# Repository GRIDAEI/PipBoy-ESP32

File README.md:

# Pip-Boy 3000 - ESP32-S3 Replica OS ☢️

Projekt ma na celu jak najdokładniejsze odtworzenie kultowego urządzenia z serii gier Fallout.
**Pip-Boy 3000**, znany głównie z _Fallout 3_ oraz _Fallout: New Vegas_, zyskuje tu nowe życie dzięki mikrokontrolerowi ESP32-S3. Projekt łączy oprogramowanie (UI/UX) z fizycznym sprzętem, tworząc realistyczny rekwizyt.

## Funkcje

- **Płynny Interfejs i Animacje**: Wykorzystanie biblioteki [LovyanGFX](https://github.com/lovyan03/LovyanGFX) zapewnia wysoką wydajność renderowania na ekranie.
- **System Audio I2S**: Autentyczne efekty dźwiękowe interfejsu (kliknięcia, przejścia w menu) odtwarzane przez `ESP8266Audio` i miksowane w czasie rzeczywistym.
- **Pełna Nawigacja**: Enkoder obrotowy, przełącznik obrotowy oraz fizyczne przyciski idealnie zmapowane, co pozwala na nawigację po zakładkach Statystyk, Ekwipunku i Danych, dokładnie tak jak w grze.
- **Ładowanie Obrazów do PSRAM**: Wysokiej rozdzielczości sprite'y (mapy, przedmioty) ładowane dynamicznie do 8MB pamięci PSRAM w celu oszczędzania pamięci RAM.
- **Zegar Czasu Rzeczywistego (RTC)**: Zegar systemowy z możliwością dostosowania i zapisem w pamięci NVS, odporny na restarty.
- **Motywy Kolorystyczne**: Obsługa różnych kolorów interfejsu (Klasyczny Zielony, Bursztynowy, Quantum Blue).
- **Oszczędzanie Energii**: Inteligentne wykrywanie bezczynności obniża taktowanie procesora do 80MHz, by oszczędzać baterię podczas długich wędrówek po Pustkowiach.

## Gotowe Płytki PCB

W projekcie zawarto pliki produkcyjne dla autorskich płytek drukowanych (PCB). Dostępne są **2 wersje** płytki, z czego **najnowsza rewizja v3.0 jest wysoce zalecana** ze względu na znaczne poprawki stabilności układu.

## Dokumentacja Projektu

Szczegółowe informacje techniczne oraz instrukcje zostały wydzielone do osobnych plików, aby ułatwić nawigację po repozytorium:

- **[Sprzęt i Elektronika (Hardware)](docs/HARDWARE.md)** – schemat układu, kompletna lista komponentów (BOM), tabela podłączeń pinów oraz informacje o zastosowanych modułach (wibracje, DAC).
- **[Architektura Oprogramowania (Software)](docs/SOFTWARE.md)** – objaśnienie działania interfejsu wizualnego (LovyanGFX), buforowanie tekstur w PSRAM, obsługa przerwań enkodera oraz zarządzanie dźwiękiem z LittleFS.
- **[Instrukcja Budowy (Build Guide)](docs/BUILD_GUIDE.md)** – przewodnik krok po kroku, jak skompilować projekt, skonfigurować środowisko PlatformIO i wgrać wymagany obraz pamięci Flash.

## 📁 Struktura Projektu

- `/src/screens/` - Logika odpowiedzialna za poszczególne zakładki interfejsu (Status, S.P.E.C.I.A.L, Ekwipunek, Mapy).
- `/src/modules/` - Sterowniki modułów takich jak Audio (I2S), Enkoder i obsługa karty SD.
- `/src/imgs/` - Tekstury, sprite'y i tablice z grafikami przygotowanymi do użycia.
- `/docs/` - Rozszerzona dokumentacja techniczna projektu.
- `main.cpp` - Główna pętla programu, sekwencja startowa (Boot OS) i dystrybucja wejść.

## Licencja

To jest projekt fanowski. _Pip-Boy_, _Vault Boy_ oraz _Fallout_ są zarejestrowanymi znakami towarowymi Bethesda Softworks LLC. Projekt został stworzony wyłącznie w celach edukacyjnych oraz hobbystycznych (cosplay).

---

_"Prepared for the Future"_ -- Vault-Tec Corporation

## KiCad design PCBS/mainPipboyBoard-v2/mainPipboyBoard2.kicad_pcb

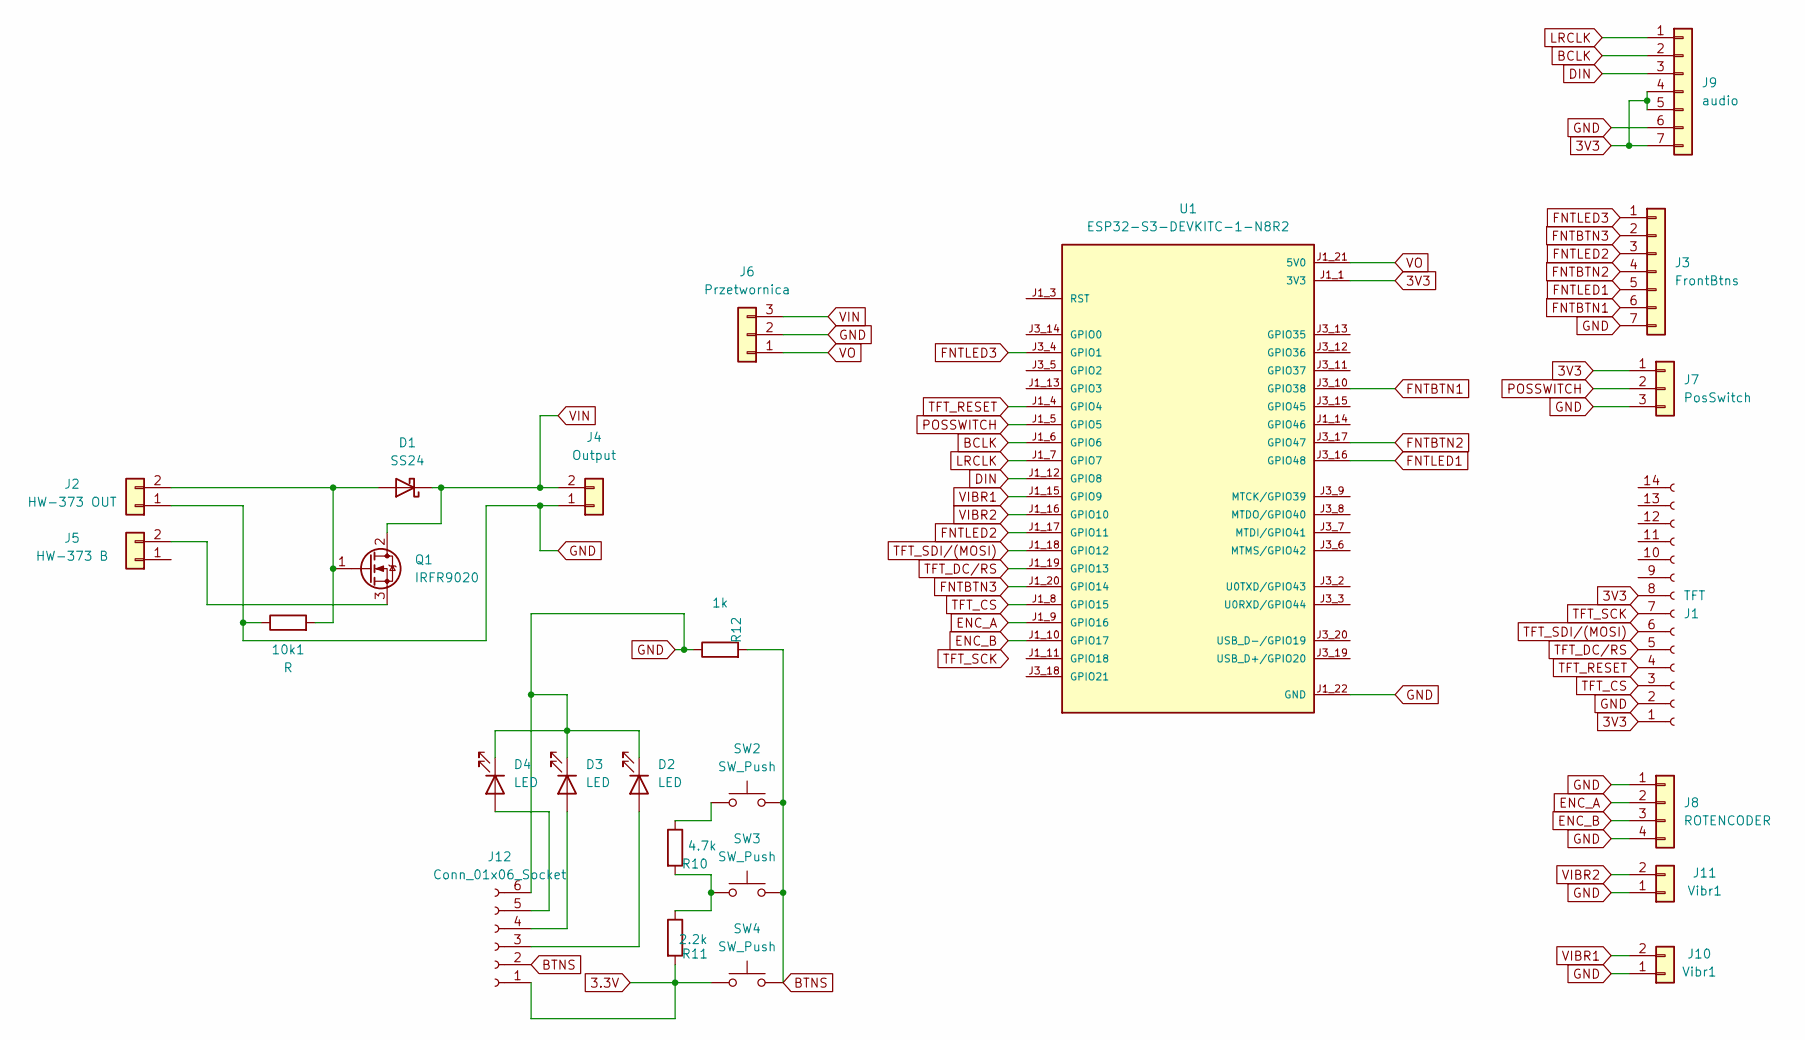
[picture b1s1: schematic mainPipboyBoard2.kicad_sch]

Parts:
10k1: R; R_1206_3216Metric_Pad1.30x1.75mm_HandSolder
D1: SS24; D_SMA
D2, D3, D4: LED; LED_1206_3216Metric_Pad1.42x1.75mm_HandSolder
J1: TFT; PinSocket_1x14_P2.54mm_Vertical
J2: HW-373 OUT; PinSocket_1x02_P2.54mm_Vertical
J3: FrontBtns; PinSocket_1x07_P2.54mm_Vertical
J4: Output; PinSocket_1x02_P2.54mm_Vertical
J5: HW-373 B; PinSocket_1x02_P2.54mm_Vertical
J6: Przetwornica; PinSocket_1x03_P2.54mm_Vertical
J7: PosSwitch; PinSocket_1x03_P2.54mm_Vertical
J8: ROTENCODER; PinSocket_1x04_P2.54mm_Vertical
J9: audio; PinSocket_1x07_P2.54mm_Vertical
J10, J11: Vibr1; PinSocket_1x02_P2.54mm_Vertical
J12: Conn_01x06_Socket; PinHeader_1x06_P2.54mm_Vertical_SMD_Pin1Right
Q1: IRFR9020; TO-252-2
R10: 4.7k; L_1206_3216Metric_Pad1.22x1.90mm_HandSolder
R11: 2.2k; L_1206_3216Metric_Pad1.22x1.90mm_HandSolder
R12: 1k; L_1206_3216Metric_Pad1.22x1.90mm_HandSolder
SW2, SW3, SW4: SW_Push; PTS810SJM250SMTRLFS
U1: ESP32-S3-DEVKITC-1-N8R2; XCVR_ESP32-S3-DEVKITC-1-N8R2; PARTREV V1

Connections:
3.3V: J12.1, R11.2, SW4.1
3V3: J1.1, J1.8, J7.1, J9.4, J9.5, J9.7, U1.J1_1 (3V3), U1.J1_2 (3V3)
BCLK: J9.2, U1.J1_6 (GPIO6)
BTNS: J12.2, R12.2, SW2.2, SW3.2, SW4.2
DIN: J9.3, U1.J1_12 (GPIO8)
ENC_A: J8.2, U1.J1_9 (GPIO16)
ENC_B: J8.3, U1.J1_10 (GPIO17)
FNTBTN1: J3.6, U1.J3_10 (GPIO38)
FNTBTN2: J3.4, U1.J3_17 (GPIO47)
FNTBTN3: J3.2, U1.J1_20 (GPIO14)
FNTLED1: J3.5, U1.J3_16 (GPIO48)
FNTLED2: J3.3, U1.J1_17 (GPIO11)
FNTLED3: J3.1, U1.J3_4 (GPIO1)
GND: 10k1.1, D2.1 (K), D3.1 (K), D4.1 (K), J1.2, J2.1, J3.7, J4.1, J6.2, J7.3, J8.1, J8.4, J9.6, J10.1, J11.1, J12.6, R12.1, U1.J1_22 (GND), U1.J3_1 (GND), U1.J3_21 (GND), U1.J3_22 (GND)
LRCLK: J9.1, U1.J1_7 (GPIO7)
unnamed: 10k1.2, D1.2 (A), J2.2, Q1.1 (G)
unnamed: D2.2 (A), J12.3
unnamed: D3.2 (A), J12.4
unnamed: D4.2 (A), J12.5
unnamed: J5.2 (Pin_2_2), Q1.3 (S)
unnamed: R10.1, SW2.1
unnamed: R10.2, R11.1, SW3.1
POSSWITCH: J7.2, U1.J1_5 (GPIO5)
TFT_CS: J1.3, U1.J1_8 (GPIO15)
TFT_DC/RS: J1.5, U1.J1_19 (GPIO13)
TFT_RESET: J1.4, U1.J1_4 (GPIO4)
TFT_SCK: J1.7
TFT_SDI/(MOSI): J1.6, U1.J1_18 (GPIO12)
VIBR1: J10.2, U1.J1_15 (GPIO9)
VIBR2: J11.2, U1.J1_16 (GPIO10)
VIN: D1.1 (K), J4.2, J6.3, Q1.2 (D)
VO: J6.1, U1.J1_21 (5V0)

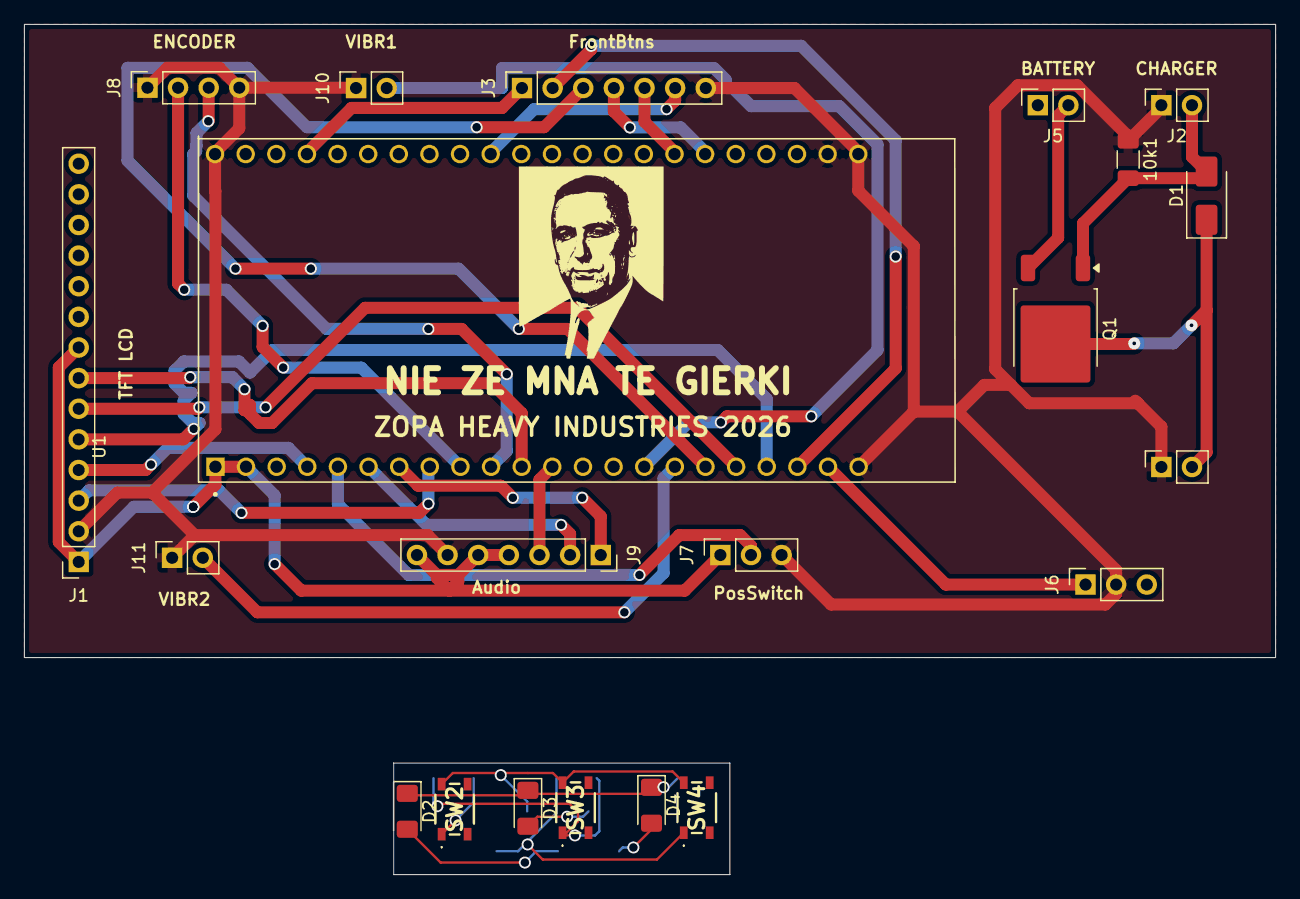
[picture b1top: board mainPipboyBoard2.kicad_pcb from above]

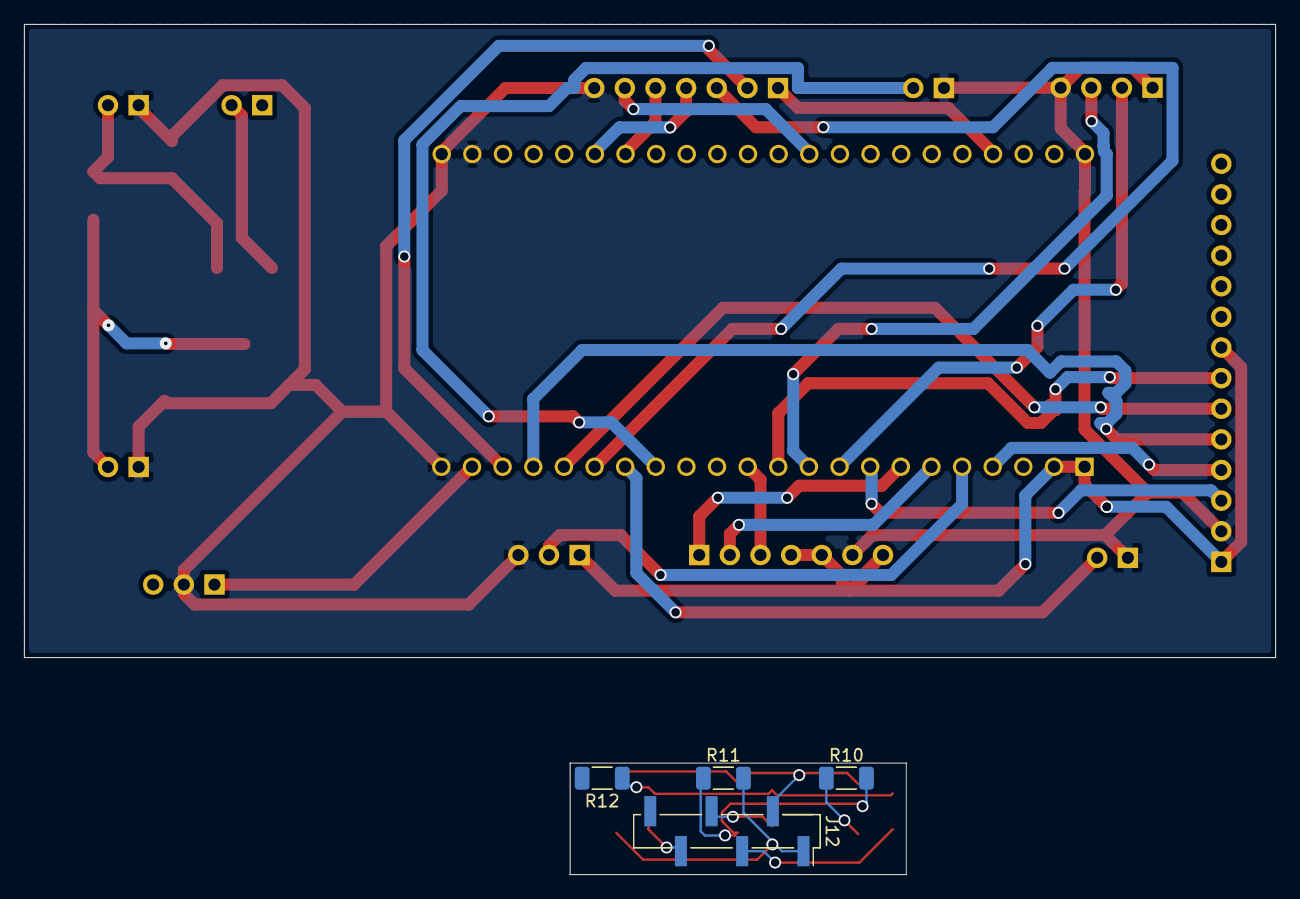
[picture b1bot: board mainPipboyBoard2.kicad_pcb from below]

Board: 2 copper layers, 103.8 x 70.5 mm, 25 parts (4 on the bottom side), 31 nets.

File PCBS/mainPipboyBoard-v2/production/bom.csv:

Designator,Footprint,Quantity,Value,LCSC Part #
10K1,1206,1,R,
D1,D_SMA,1,SS24,
J1,PinSocket_1x14_P2.54mm_Vertical,1,TFT,
"J10, J11",PinSocket_1x02_P2.54mm_Vertical,2,Vibr1,
J2,PinSocket_1x02_P2.54mm_Vertical,1,HW-373 OUT,
J3,PinSocket_1x07_P2.54mm_Vertical,1,FrontBtns,
J4,PinSocket_1x02_P2.54mm_Vertical,1,Output,
J5,PinSocket_1x02_P2.54mm_Vertical,1,HW-373 B,
J6,PinSocket_1x03_P2.54mm_Vertical,1,Przetwornica,
J7,PinSocket_1x03_P2.54mm_Vertical,1,PosSwitch,
J8,PinSocket_1x04_P2.54mm_Vertical,1,Conn_01x04,
J9,PinSocket_1x07_P2.54mm_Vertical,1,audio,
Q1,TO-252-2,1,IRFR9020,
U1,XCVR_ESP32-S3-DEVKITC-1-N8R2,1,ESP32-S3-DEVKITC-1-N8R2,

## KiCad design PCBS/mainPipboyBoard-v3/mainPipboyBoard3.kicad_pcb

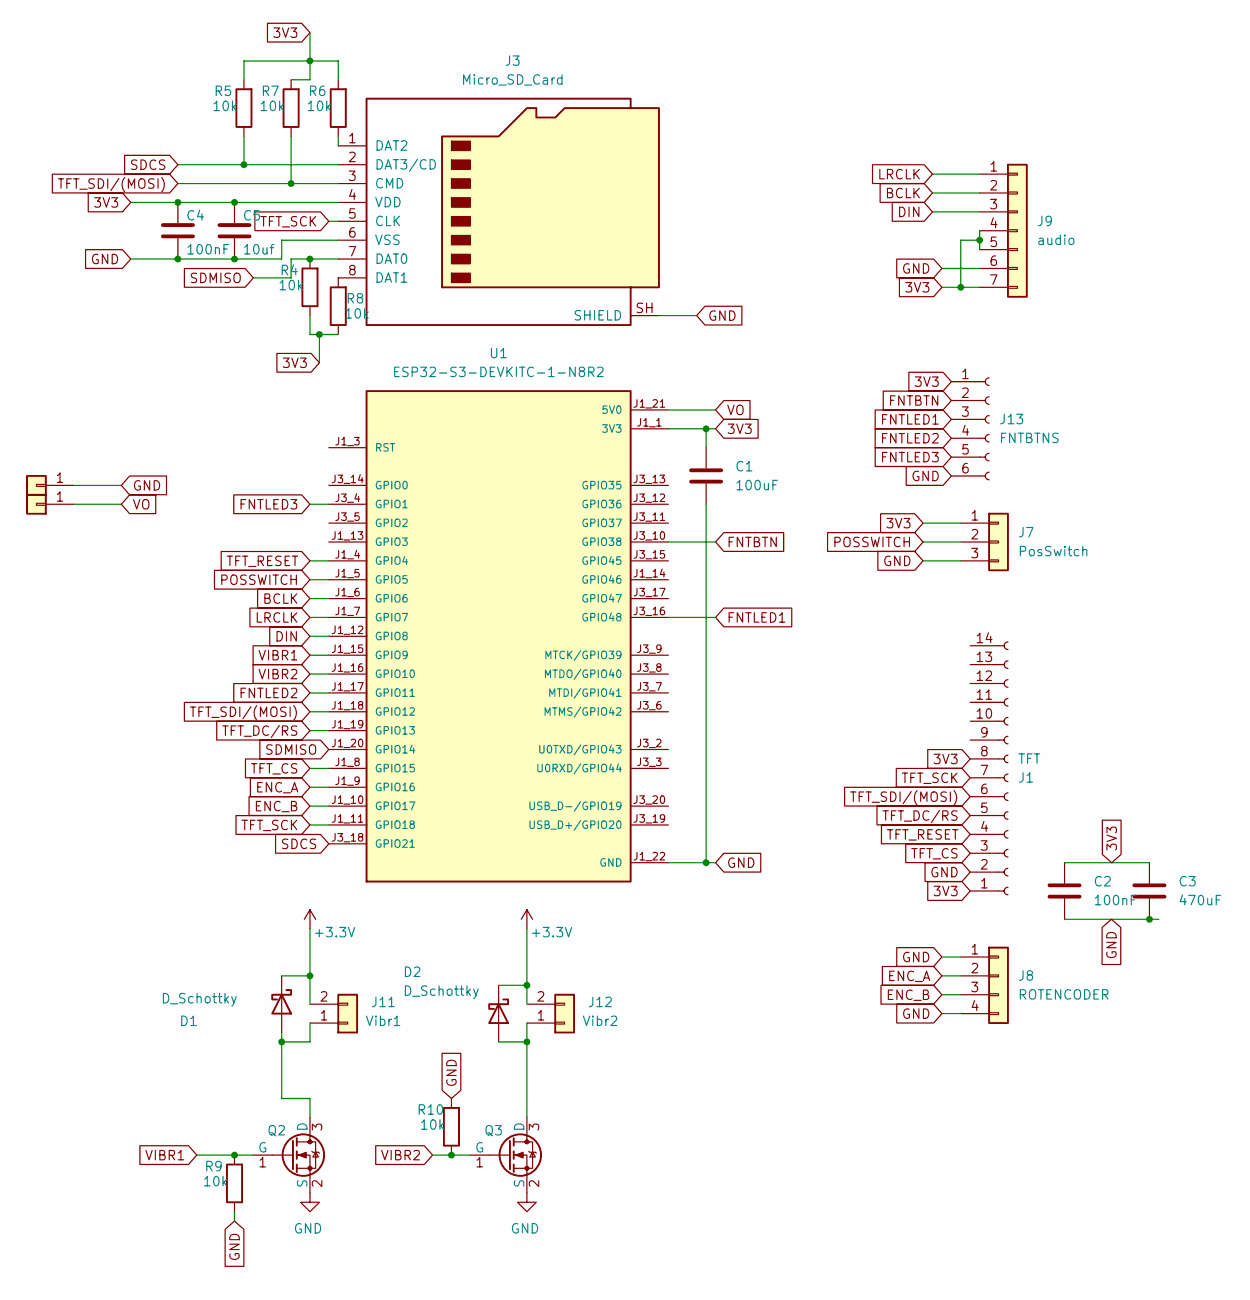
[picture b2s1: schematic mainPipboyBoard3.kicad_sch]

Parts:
C1: 100uF; C_Radial_D4.0mm_H5.0mm_P1.50mm
C2: 100nF; C_0805_2012Metric_Pad1.18x1.45mm_HandSolder
C3: 470uF; C_Radial_D4.0mm_H5.0mm_P1.50mm
C4: 100nF; L_1206_3216Metric_Pad1.22x1.90mm_HandSolder
C5: 10uf; L_1206_3216Metric_Pad1.22x1.90mm_HandSolder
D1, D2: D_Schottky; D_1206_3216Metric_Pad1.42x1.75mm_HandSolder
J1: TFT; PinSocket_1x14_P2.54mm_Vertical
J2, J4: Conn_01x01; PinSocket_1x01_P2.54mm_Vertical
J3: Micro_SD_Card; 112JTDARR01
J7: PosSwitch; PinSocket_1x03_P2.54mm_Vertical
J8: ROTENCODER; PinSocket_1x04_P2.54mm_Vertical
J9: audio; PinSocket_1x07_P2.54mm_Vertical
J11: Vibr1; PinSocket_1x02_P2.54mm_Vertical
J12: Vibr2; PinSocket_1x02_P2.54mm_Vertical
J13: FNTBTNS; JST_ZH_B6B-ZR-SM4-TF_1x06-1MP_P1.50mm_Vertical
Q2, Q3: AO3400A; SOT-23; Part AO3400A; LCSC Part Number C20917
R4, R5, R6, R7, R8, R9, R10: 10k; L_1206_3216Metric_Pad1.22x1.90mm_HandSolder
U1: ESP32-S3-DEVKITC-1-N8R2; XCVR_ESP32-S3-DEVKITC-1-N8R2; PARTREV V1

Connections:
3V3: C1.2, C2.2, C3.2, C4.1, C5.1, J1.1, J1.8, J3.4 (VDD), J7.1, J9.4, J9.5, J9.7, J13.1, R4.1, R5.2, R6.2, R7.2, R8.1, U1.J1_1 (3V3), U1.J1_2 (3V3)
+3.3V: D1.1 (K), D2.1 (K), J11.2, J12.2
BCLK: J9.2, U1.J1_6 (GPIO6)
DIN: J9.3, U1.J1_12 (GPIO8)
ENC_A: J8.2, U1.J1_9 (GPIO16)
ENC_B: J8.3, U1.J1_10 (GPIO17)
FNTBTN: J13.2, U1.J3_10 (GPIO38)
FNTLED1: J13.3, U1.J3_16 (GPIO48)
FNTLED2: J13.4, U1.J1_17 (GPIO11)
FNTLED3: J13.5, U1.J3_4 (GPIO1)
GND: C1.1, C2.1, C3.1, C4.2, C5.2, J1.2, J3.6 (VSS), J3.SH (SHIELD), J4.1 (Pin_1_1), J7.3, J8.1, J8.4, J9.6, J13.6, Q2.2 (S), Q3.2 (S), R9.1, R10.2, U1.J1_22 (GND), U1.J3_1 (GND), U1.J3_21 (GND), U1.J3_22 (GND)
LRCLK: J9.1, U1.J1_7 (GPIO7)
unnamed: D1.2 (A), J11.1, Q2.3 (D)
unnamed: D2.2 (A), J12.1, Q3.3 (D)
unnamed: J3.8 (DAT1), R8.2
unnamed: J3.1 (DAT2), R6.1
POSSWITCH: J7.2, U1.J1_5 (GPIO5)
SDCS: J3.2 (DAT3/CD), R5.1, U1.J3_18 (GPIO21)
SDMISO: J3.7 (DAT0), R4.2, U1.J1_20 (GPIO14)
TFT_CS: J1.3, U1.J1_8 (GPIO15)
TFT_DC/RS: J1.5, U1.J1_19 (GPIO13)
TFT_RESET: J1.4, U1.J1_4 (GPIO4)
TFT_SCK: J1.7, J3.5 (CLK), U1.J1_11 (GPIO18)
TFT_SDI/(MOSI): J1.6, J3.3 (CMD), R7.1, U1.J1_18 (GPIO12)
VIBR1: Q2.1 (G), R9.2, U1.J1_15 (GPIO9)
VIBR2: Q3.1 (G), R10.1, U1.J1_16 (GPIO10)
VO: J2.1 (Pin_1_1), U1.J1_21 (5V0)

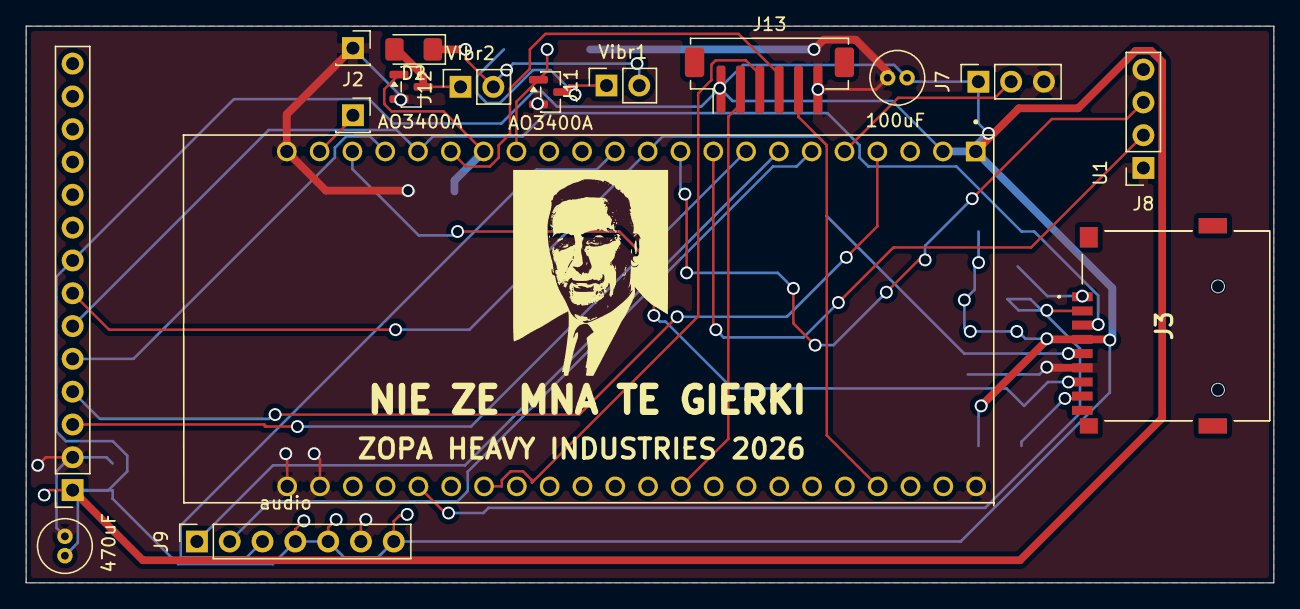
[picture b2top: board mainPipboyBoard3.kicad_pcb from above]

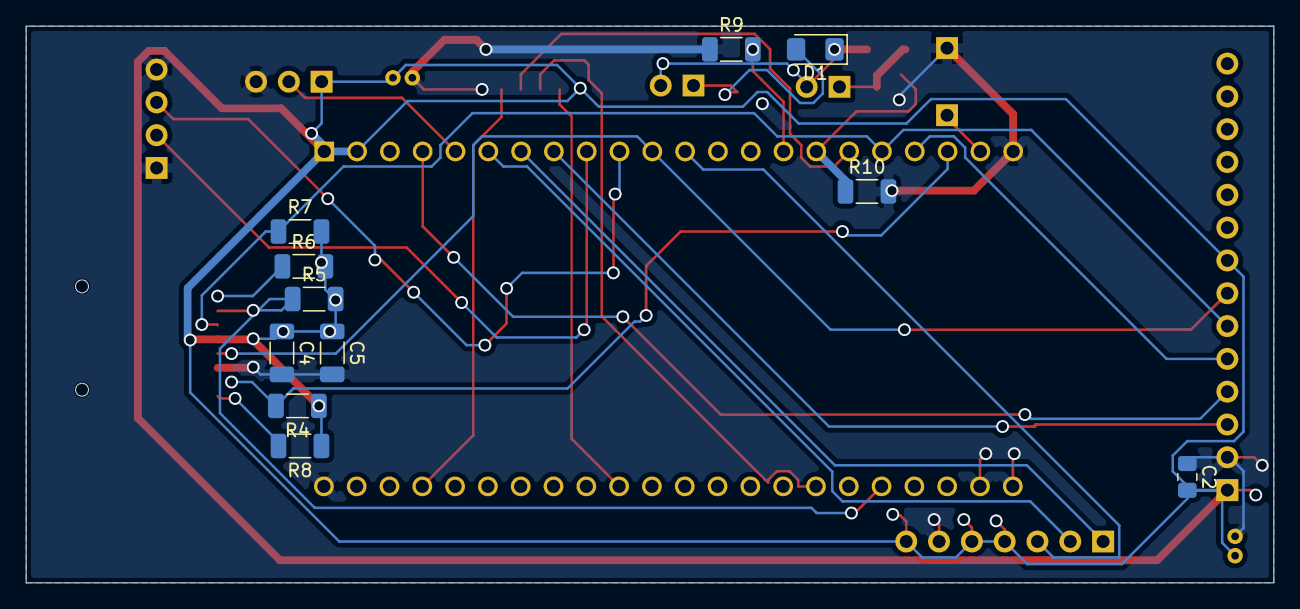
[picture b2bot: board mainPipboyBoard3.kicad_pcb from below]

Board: 2 copper layers, 96.6 x 43.1 mm, 27 parts (11 on the bottom side), 27 nets.

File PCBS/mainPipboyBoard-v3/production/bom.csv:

Designator,Footprint,Quantity,Value,LCSC Part #
C1,C_Radial_D4.0mm_H5.0mm_P1.50mm,1,100uF,
C2,0805,1,100nF,
C3,C_Radial_D4.0mm_H5.0mm_P1.50mm,1,470uF,
C4,1206,1,100nF,
C5,1206,1,10uf,
"D1, D2",1206,2,D_Schottky,
J1,PinSocket_1x14_P2.54mm_Vertical,1,TFT,
J11,PinSocket_1x02_P2.54mm_Vertical,1,Vibr1,
J12,PinSocket_1x02_P2.54mm_Vertical,1,Vibr2,
J13,JST_ZH_B6B-ZR-SM4-TF_1x06-1MP_P1.50mm_Vertical,1,FNTBTNS,
"J2, J4",PinSocket_1x01_P2.54mm_Vertical,2,Conn_01x01,
J3,112JTDARR01,1,Micro_SD_Card,
J7,PinSocket_1x03_P2.54mm_Vertical,1,PosSwitch,
J8,PinSocket_1x04_P2.54mm_Vertical,1,ROTENCODER,
J9,PinSocket_1x07_P2.54mm_Vertical,1,audio,
"Q2, Q3",SOT-23,2,AO3400A,C20917
"R10, R4, R5, R6, R7, R8, R9",1206,7,10k,
U1,XCVR_ESP32-S3-DEVKITC-1-N8R2,1,ESP32-S3-DEVKITC-1-N8R2,

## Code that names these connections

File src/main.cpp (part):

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#include "soc/rtc_cntl_reg.h"


const int FNTLED1 = 48;
const int FNTLED2 = 11;
const int FNTLED3 = 1;
const int FNTBTN_ADC_PIN = 2; 
bool fntBtn1Prev = HIGH;
bool fntBtn2Prev = HIGH;
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bool downclk = false;
bool downPrev = HIGH;

const int VIBR1_PIN = 9;
const int VIBR2_PIN = 10;
int vibr_ms = 80;

int rtc_sda = 40; // temporary placeholder, user might need to adjust if RTC moved, originally 8
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ESP32Encoder encoder;

void vibrate(int ms = vibr_ms) {
    digitalWrite(VIBR1_PIN, HIGH);
    digitalWrite(VIBR2_PIN, HIGH);
    vibroEnd = millis() + ms;
}

void handleVibro() {
    if (vibroEnd > 0 && millis() >= vibroEnd) {
        digitalWrite(VIBR1_PIN, LOW);
        digitalWrite(VIBR2_PIN, LOW);
        vibroEnd = 0;
    }
}
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  unsigned long intro_start = millis(); 


  pinMode(FNTLED1, OUTPUT);
  pinMode(FNTLED2, OUTPUT);
  pinMode(FNTLED3, OUTPUT);
  updateFrontLeds(section_id);
  
  pinMode(FNTBTN_ADC_PIN, INPUT);
  
  pinMode(upbtn, INPUT_PULLUP);
  pinMode(downbtn, INPUT_PULLUP);
  pinMode(VIBR1_PIN, OUTPUT);
  pinMode(VIBR2_PIN, OUTPUT);
  pinMode(selectBtn, INPUT_PULLUP);
  digitalWrite(VIBR1_PIN, LOW);
  digitalWrite(VIBR2_PIN, LOW);


  ESP32Encoder::useInternalWeakPullResistors = puType::up;
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
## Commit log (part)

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2026-03-30 start
2026-04-05 fuck me man co to jest
2026-04-05 Zrobienie SPECIAl OOP
2026-04-07 dddd
2026-04-07 trying to fix ts
2026-04-09 dodatki bonus essa
2026-04-13 suchanupdate
2026-04-13 feef
2026-04-28 Ostatnie zmiany
2026-04-29 jadom
